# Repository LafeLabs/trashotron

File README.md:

# TRASHOTRON

## [GITHUB.COM/LAFELABS/TRASHOTRON](https://github.com/lafelabs/trashotron)

## [LOCALHOST](http://localhost/)

THIS IS THE UNIFICATION OF GEOMETRON AND TRASH MAGIC IN A SELF-REPLICATING SET

# TRASHOTRON OPTICAL NEURON

 - [boards/trashotron-optical-neuron.brd](boards/trashotron-optical-neuron.brd)
 - [boards/trashotron-optical-neuron.sch](boards/trashotron-optical-neuron.sch) 
 - [buy pcb's at pcbway.com](https://www.pcbway.com/project/shareproject/W224521BSI37_trashotron_optical_neuron_2023_03_06_ae2b0405.html)

### FOR THE LID CUT OUT A 3"X4.5" CARDBOARD RECTANGLE, PAINT AS SHOWN  WITH 1.5 INCH SQURES:

### LAYOUT OF STACK:

### CUT OUT THREE LAYERS OF THESE AND STACK THEM ABOVE THE BOARD 

### BOARD DIMENSIONS:

### LAYER WITH PHOTODIOES PUSHED THROUGH SLITS CUT WITH BOX CUTTER:

### 2 LAYERS OF CARDBOARD WITH 1 INCH SQUARES CUT OUT:

# TRASHOTRON DRIVER

 - [boards/trashotron-driver.brd](boards/trashotron-driver.brd)
 - [boards/trashotron-driver.sch](boards/trashotron-driver.sch) 
 - [link to buy from pcbway.com](www.pcbway.com/project/shareproject/W224521BSI42_trashotron_driver_2023_03_06_1aff405c.html)

Materials

 - [3x$12 = $36 pololu robotics stepper driver](https://www.pololu.com/product/2966)
 - [$15 bojack capacitor kit](https://www.amazon.com/BOJACK-Ceramic-Capacitor-Assortment-Capacitors/dp/B07P7HRGT9/)
 - [$6.32 10k resistors 100 units](https://www.amazon.com/Projects-100EP51210K0-10k-Resistors-Pack/dp/B0185FIOTA/)
 - [$10 50 pin 0.1 inch pitch right angle header strips](https://www.amazon.com/Yohii-Single-Right-Header-Connector/dp/B07C89T16T/)
 - [$7 50 units LM358P op amps](https://www.amazon.com/BOJACK-LM358P-Operational-Amplifier-LM358N/dp/B07WQWPLSP/)
 - [ribbon cable from amazon](https://www.amazon.com/Eowpower-16-5Ft-20Pin-Rainbow-Ribbon/dp/B01NC2L2WB/)

# TRASHOTRON SLIMEZISTOR (ANALOG)
 
The SlimeZistor is a relaxation oscillator which uses an LM358P op amp to charge and discharge a capacitor through some sample which is connected to the two probe wires.  The schematic is as follows, and should be copied and pasted on the bottom of each unit:

These are the kit parts:

Here are links to buy the parts from amazon(enough for about 50 units for about 40 dollars):

 - [$15 bojack capacitor kit](https://www.amazon.com/BOJACK-Ceramic-Capacitor-Assortment-Capacitors/dp/B07P7HRGT9/)
 - [$6.32 10k resistors 100 units](https://www.amazon.com/Projects-100EP51210K0-10k-Resistors-Pack/dp/B0185FIOTA/)
 - [$10 50 pin 0.1 inch pitch right angle header strips](https://www.amazon.com/Yohii-Single-Right-Header-Connector/dp/B07C89T16T/)
 - [$7 50 units LM358P op amps](https://www.amazon.com/BOJACK-LM358P-Operational-Amplifier-LM358N/dp/B07WQWPLSP/)

### [$90 Digikey cart link with part set for 100 units](https://www.digikey.com/short/44n3w1tp)

The circuit board is a 1x2 inch rectangle cut out of thin cardboard like a cereal box:

Remove pins 1,2, and 3 of the 8 pin IC:

Assemble as follows, with 0.1 uF capacitor to the far left, then 1 uF and then the two to the far right which are horizontal are the 10 uF capacitors:

This is a 5x blowup of the board, with parts labeled. Replicate this as a tool for replication to carry with you as you replicate the set:

An array can also be cut out using a laser cutter with the following .svg file(cut out a 4 inch square of this, with the blue layer as raster and black layer as cut):

Here is an .svg of just one board:

This is what the bottom looks like after full assembly:

The enclosure is made from 4 squares each 4x4 inches in size cut from corrugated cardboard using the tools of Geometron:

Stack and glue with Elmer's glue or wheat paste:

Second layer:

Add the circuit board to the box before adding the lid:

Full assembly with lid and rubber bands:

Fully assembled system with speaker connected to audio output and a solar panel connected to the USB power:

## TRASHOTRON SLIMEZISTOR(ANALOG, PCB)

 - [boards/trashotron-slimezistor.brd](boards/trashotron-slimezistor.brd)
 - [boards/trashotron-slimezistor.sch](boards/trashotron-slimezistor.sch) 
 - [buy boards from pcbway.com](https://www.pcbway.com/project/shareproject/SlimeZistor_d6c918ee.html)
 - [wikipedia link about relaxation oscillator](https://en.wikipedia.org/wiki/Relaxation_oscillator)

The board is 2x1 inch and it fits in a cavity centered in a 3 inch by 3 inch cardboard square with ports as shown.  Find USB and audio in the trash and another cable from the trash with two wires .  This can run on a direct solar panel, since it should work at random voltages.    

## RESISTOR AND CAPACITOR ORDER

 - [30M resistor](https://www.digikey.com/en/products/detail/yageo/HHV-25FR-52-30M/2813033)
 - [10 k resistor](https://www.digikey.com/en/products/detail/stackpole-electronics-inc/CF18JT10K0/1741566)
 - [0.1 uF capacitor](https://www.digikey.com/en/products/detail/kyocera-avx/SR211C104KARTR1/3066560)
 - [0.47 uF capacitor](https://www.digikey.com/en/products/detail/kyocera-avx/SR215E474MAR/1836459)
 - [10 uF capacitor](https://www.digikey.com/en/products/detail/kemet/C322C106K3R5TA/6562379)
 - [link to whole digikey cart](https://www.digikey.com/short/44n3w1tp)
 
## TRASHOTRON HOMESCREEN

## TRASHOTRON HYPERCUBE

self-replicating cubes from cardboard trash based on a 4 inch by 4 inch square.

 - [boards/trashotron-hypercube-v1.brd](boards/trashotron-hypercube.brd)
 - [boards/trashotron-hypercube-v1.sch](boards/trashotron-hypercube.sch)

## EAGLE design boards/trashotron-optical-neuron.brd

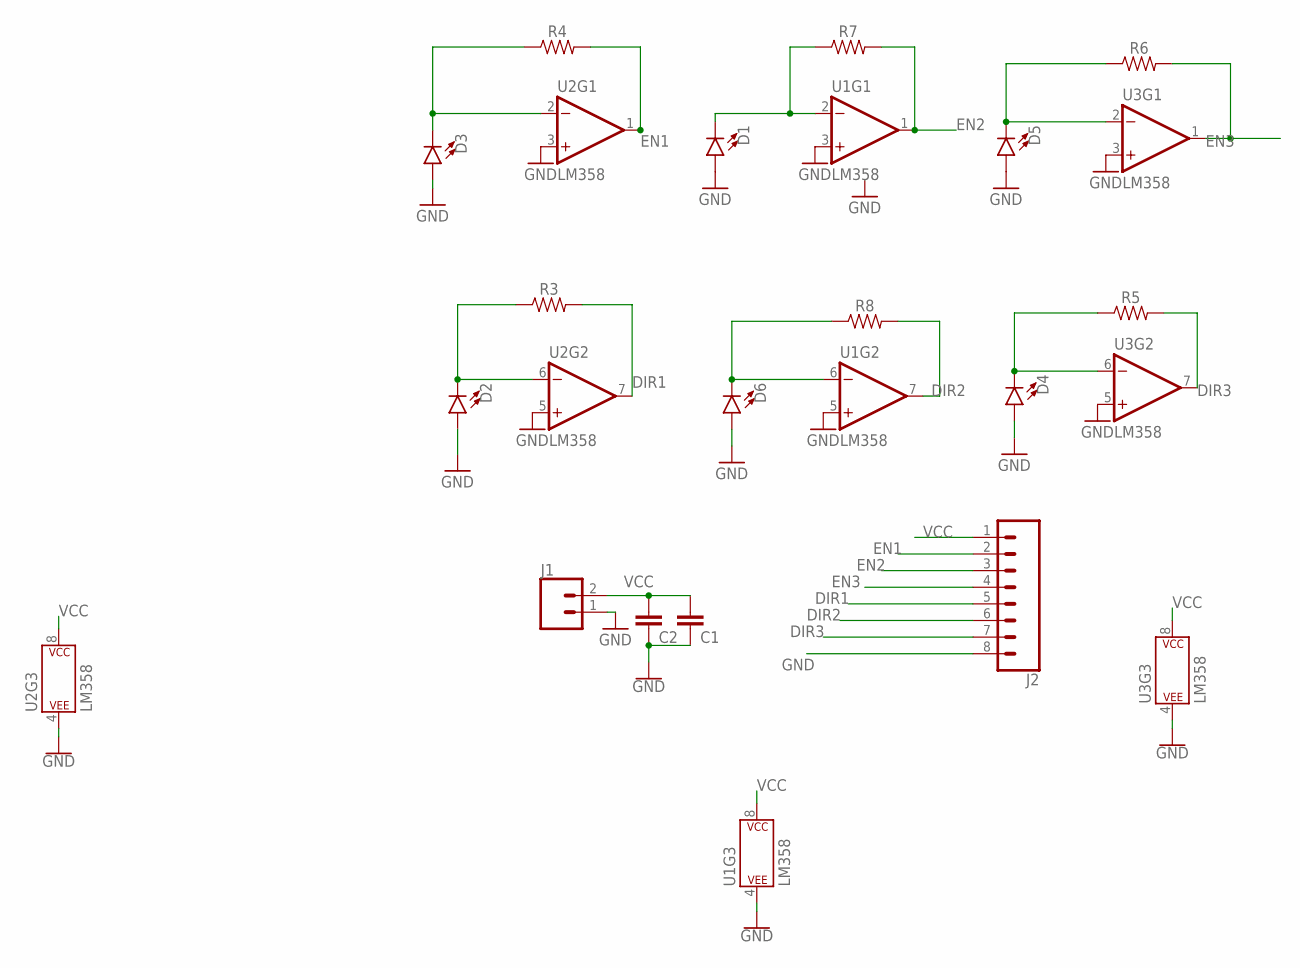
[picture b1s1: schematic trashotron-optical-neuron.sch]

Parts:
C1, C2: C-EU050-050X075; C050-050X075
D1, D2, D3, D4, D5, D6: LED3MM; LED_3MM
J1: CONN_02; 1X02
J2: CONN_08"; 1X08
R3, R4, R5, R6, R7, R8: AXIAL-0.3
U1, U2, U3: LM358; DIP08

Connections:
DIR1: J2.5, R3.P$2 (2), U2.7 (OUT)
DIR2: J2.6, R8.P$2 (2), U1.7 (OUT)
DIR3: J2.7, R5.P$2 (2), U3.7 (OUT)
EN1: J2.2, R4.P$2 (2), U2.1 (OUT)
EN2: J2.3, R7.P$2 (2), U1.1 (OUT)
EN3: J2.4, R6.P$2 (2), U3.1 (OUT)
GND: C1.1, C2.1, D1.A, D2.A, D3.A, D4.A, D5.A, D6.A, J1.1, J2.8, U1.3 (+IN), U1.4 (P$V-), U1.5 (+IN), U2.3 (+IN), U2.4 (P$V-), U2.5 (+IN), U3.3 (+IN), U3.4 (P$V-), U3.5 (+IN)
unnamed: D1.K (C), R7.P$1 (1), U1.2 (-IN)
unnamed: D3.K (C), R4.P$1 (1), U2.2 (-IN)
unnamed: D2.K (C), R3.P$1 (1), U2.6 (-IN)
unnamed: D4.K (C), R5.P$1 (1), U3.6 (-IN)
unnamed: D5.K (C), R6.P$1 (1), U3.2 (-IN)
unnamed: D6.K (C), R8.P$1 (1), U1.6 (-IN)
VCC: C1.2, C2.2, J1.2, J2.1, U1.8 (P$V+), U2.8 (P$V+), U3.8 (P$V+)

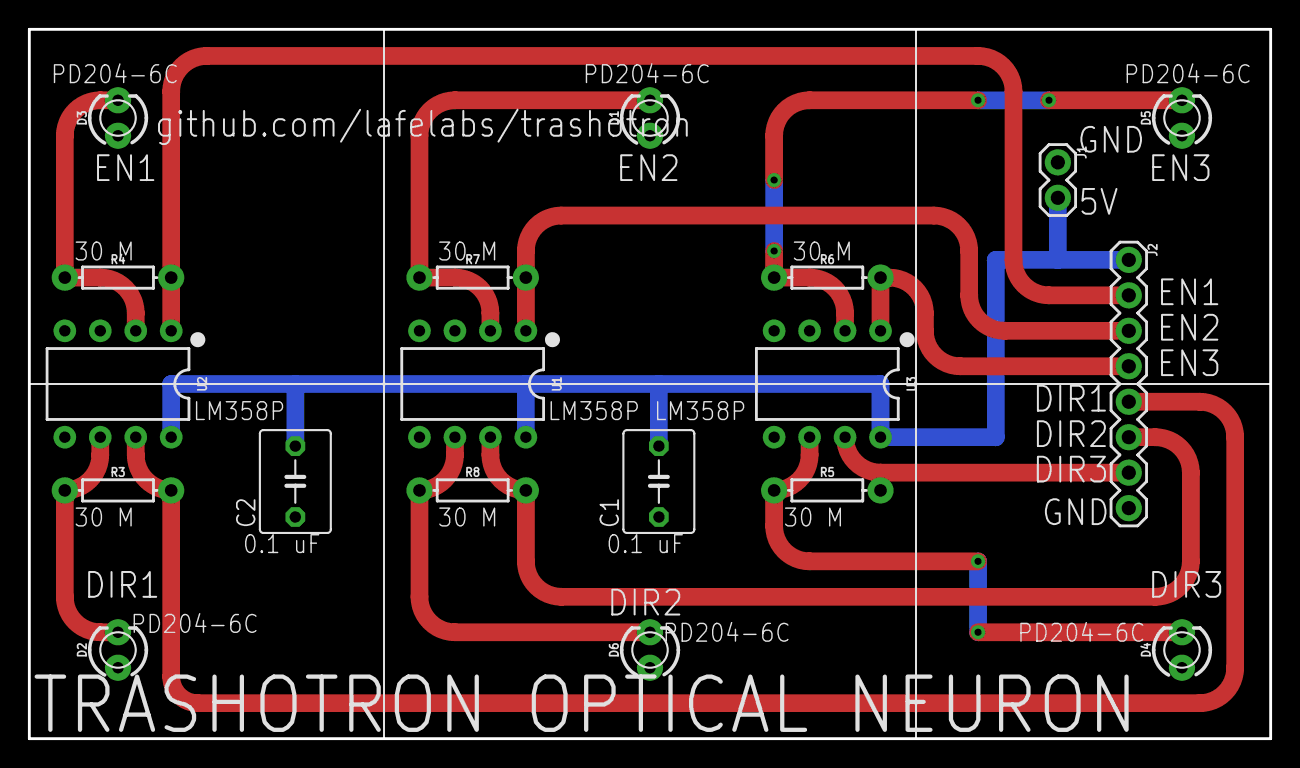
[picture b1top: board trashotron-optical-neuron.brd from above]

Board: 2 copper layers, 88.9 x 50.8 mm, 19 parts (0 on the bottom side), 14 nets.

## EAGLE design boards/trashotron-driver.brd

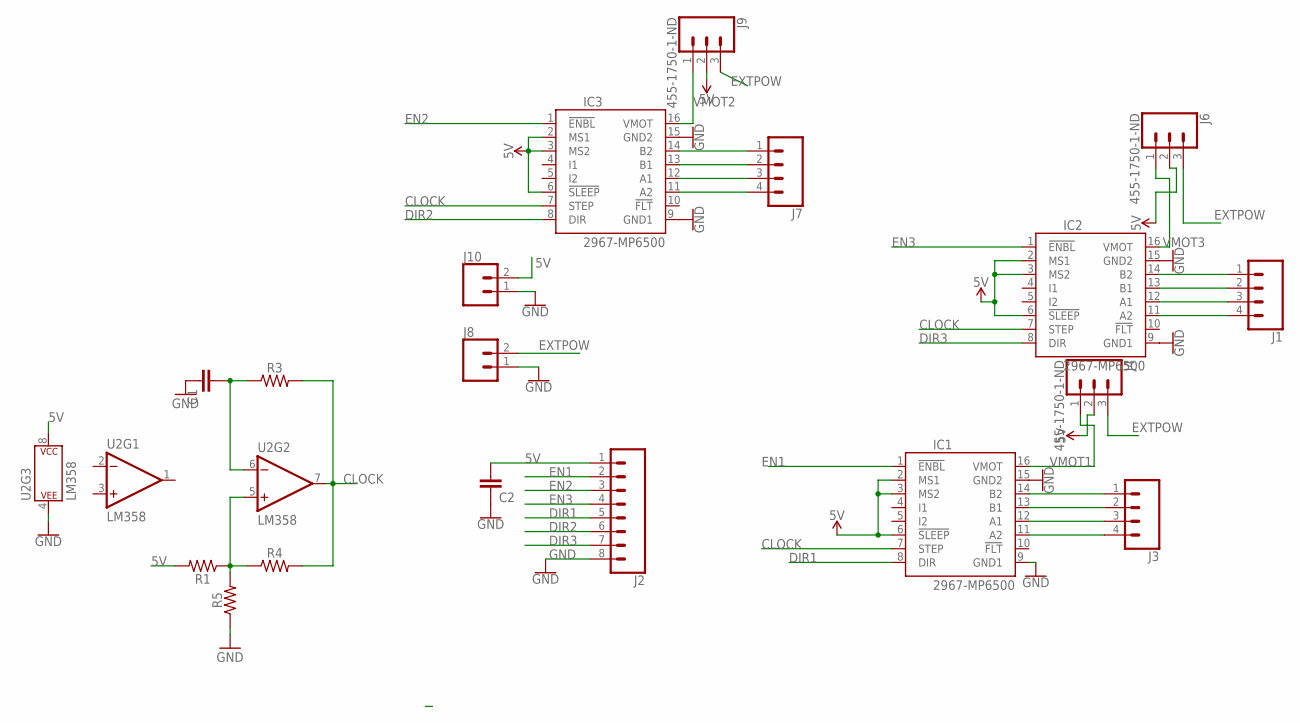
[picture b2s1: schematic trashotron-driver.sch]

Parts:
C1, C2: C-EU050-050X075; C050-050X075
IC1, IC2, IC3: 2967-MP6500; MP6500
J1, J3, J7: CONN_04; 1X04
J2: CONN_08"; 1X08
J4, J6, J9: 455-1750-1-ND; 1X03
J8, J10: CONN_02; 1X02
R1, R3, R4, R5: AXIAL-0.3
U2: LM358; DIP08

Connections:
5V: C2.2, IC1.2 (MS1), IC1.3 (MS2), IC1.6 (!SLEEP), IC2.2 (MS1), IC2.3 (MS2), IC2.6 (!SLEEP), IC3.2 (MS1), IC3.3 (MS2), IC3.6 (!SLEEP), J2.1, J4.2, J6.2, J9.2, J10.2, R1.P$2 (2), U2.8 (P$V+)
CLOCK: IC1.7 (STEP), IC2.7 (STEP), IC3.7 (STEP), R3.P$2 (2), R4.P$2 (2), U2.7 (OUT)
DIR1: IC1.8 (DIR), J2.5
DIR2: IC3.8 (DIR), J2.6
DIR3: IC2.8 (DIR), J2.7
EN1: IC1.1 (!ENBL), J2.2
EN2: IC3.1 (!ENBL), J2.3
EN3: IC2.1 (!ENBL), J2.4
EXTPOW: J4.3, J6.3, J8.2, J9.3
GND: C1.1, C2.1, IC1.9 (GND1), IC1.15 (GND2), IC2.9 (GND1), IC2.15 (GND2), IC3.9 (GND1), IC3.15 (GND2), J2.8, J8.1, J10.1, R5.P$1 (1), U2.4 (P$V-)
unnamed: IC3.14 (B2), J7.1
unnamed: IC3.13 (B1), J7.2
unnamed: IC1.14 (B2), J3.1
unnamed: IC1.13 (B1), J3.2
unnamed: IC1.12 (A1), J3.3
unnamed: IC1.11 (A2), J3.4
unnamed: IC2.14 (B2), J1.1
unnamed: IC2.13 (B1), J1.2
unnamed: IC2.12 (A1), J1.3
unnamed: IC2.11 (A2), J1.4
unnamed: IC3.12 (A1), J7.3
unnamed: IC3.11 (A2), J7.4
unnamed: C1.2, R3.P$1 (1), U2.6 (-IN)
unnamed: R1.P$1 (1), R4.P$1 (1), R5.P$2 (2), U2.5 (+IN)
VMOT1: IC1.16 (VMOT), J4.1
VMOT2: IC3.16 (VMOT), J9.1
VMOT3: IC2.16 (VMOT), J6.1

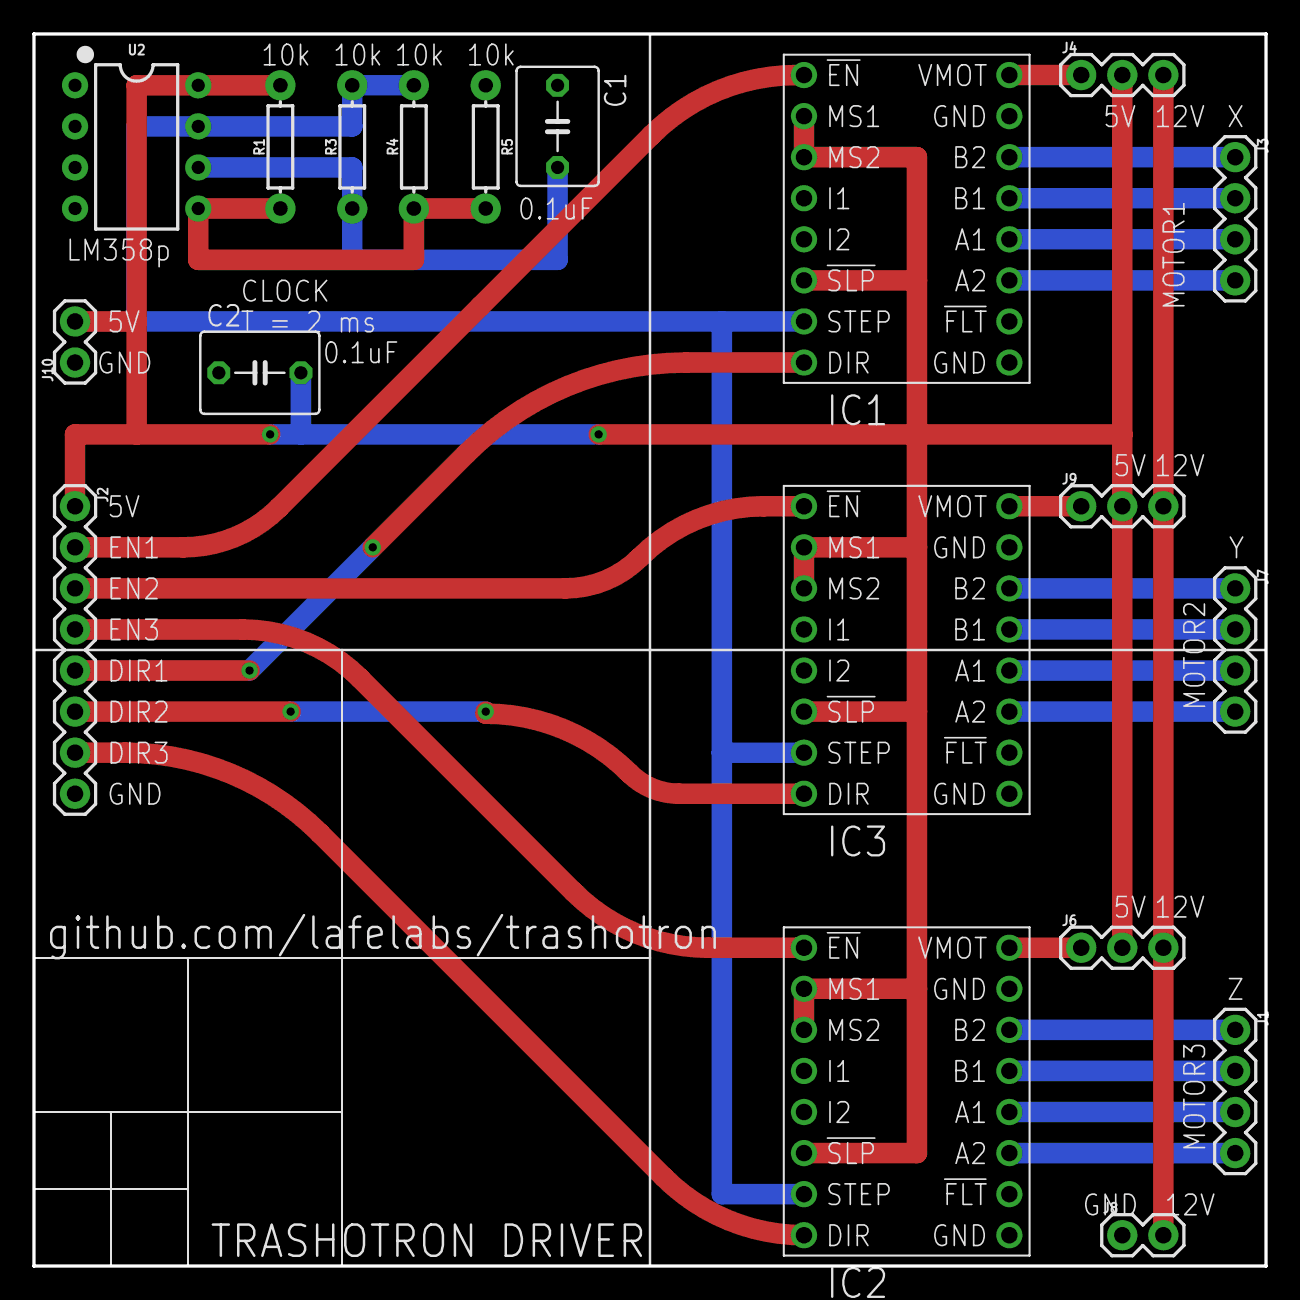
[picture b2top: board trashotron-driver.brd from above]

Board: 2 copper layers, 76.2 x 76.2 mm, 19 parts (0 on the bottom side), 27 nets.

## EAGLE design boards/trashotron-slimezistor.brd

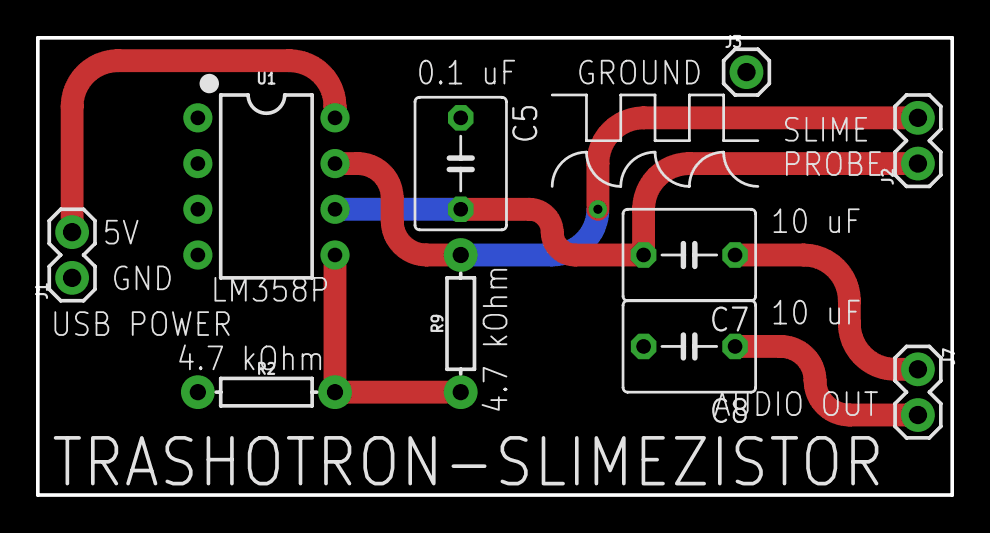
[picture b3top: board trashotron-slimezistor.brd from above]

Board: 2 copper layers, 50.8 x 25.4 mm, 10 parts (0 on the bottom side), 7 nets.

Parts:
C5, C7, C8: C050-050X075
J1, J2, J7: 1X02
J3: 1X01
R2, R9: AXIAL-0.3
U1: LM358; DIP08

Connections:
GND: C5.1, C8.2, J1.1, J3.1, R2.P$1, U1.4
unnamed: J2.2, R9.P$2, U1.7
unnamed: R2.P$2, R9.P$1, U1.5
unnamed: C5.2, C7.2, J2.1, U1.6
unnamed: C8.1, J7.2
unnamed: C7.1, J7.1
VCC: J1.2, U1.8

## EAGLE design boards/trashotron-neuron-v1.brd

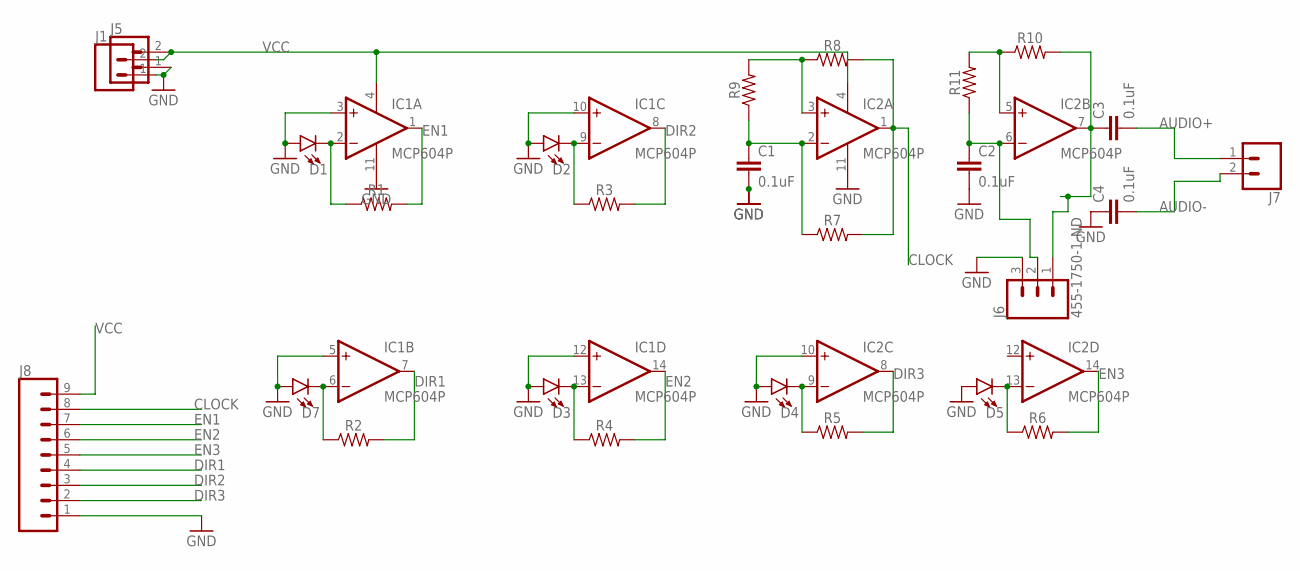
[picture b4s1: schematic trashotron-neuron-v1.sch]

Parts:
C1, C2, C3, C4: 0.1uF; CAP-PTH-SMALL-KIT
D1, D2, D3, D4, D5, D7: LED3MM; LED_3MM
IC1, IC2: MCP604P; DIL14
J1, J5, J7: CONN_02; 1X02
J6: 455-1750-1-ND; 1X03
J8: CONN_09; 1X09
R1, R2, R3, R4, R5, R6, R7, R8, R9, R10, R11: AXIAL-0.3

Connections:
AUDIO+: C3.2, J7.1
AUDIO-: C4.2, J7.2
CLOCK: IC2.1 (OUT), J8.8, R7.P$2 (2), R8.P$2 (2)
DIR1: IC1.7 (OUT), J8.4, R2.P$2 (2)
DIR2: IC1.8 (OUT), J8.3, R3.P$2 (2)
DIR3: IC2.8 (OUT), J8.2, R5.P$2 (2)
EN1: IC1.1 (OUT), J8.7, R1.P$2 (2)
EN2: IC1.14 (OUT), J8.6, R4.P$2 (2)
EN3: IC2.14 (OUT), J8.5, R6.P$2 (2)
GND: C1.2, C2.2, C4.1, D1.A, D2.A, D3.A, D4.A, D5.A, D7.A, IC1.3 (+IN), IC1.5 (+IN), IC1.10 (+IN), IC1.11 (V-), IC1.12 (+IN), IC2.10 (+IN), IC2.11 (V-), J1.1, J5.1, J6.3, J8.1
unnamed: D1.K (C), IC1.2 (-IN), R1.P$1 (1)
unnamed: D7.K (C), IC1.6 (-IN), R2.P$1 (1)
unnamed: D2.K (C), IC1.9 (-IN), R3.P$1 (1)
unnamed: D4.K (C), IC2.9 (-IN), R5.P$1 (1)
unnamed: D5.K (C), IC2.13 (-IN), R6.P$1 (1)
unnamed: D3.K (C), IC1.13 (-IN), R4.P$1 (1)
unnamed: C2.1, IC2.6 (-IN), J6.2, R11.P$1 (1)
unnamed: IC2.3 (+IN), R8.P$1 (1), R9.P$2 (2)
unnamed: IC2.5 (+IN), R10.P$1 (1), R11.P$2 (2)
unnamed: C1.1, IC2.2 (-IN), R7.P$1 (1), R9.P$1 (1)
unnamed: C3.1, IC2.7 (OUT), J6.1, R10.P$2 (2)
VCC: IC1.4 (V+), IC2.4 (V+), J1.2, J5.2, J8.9

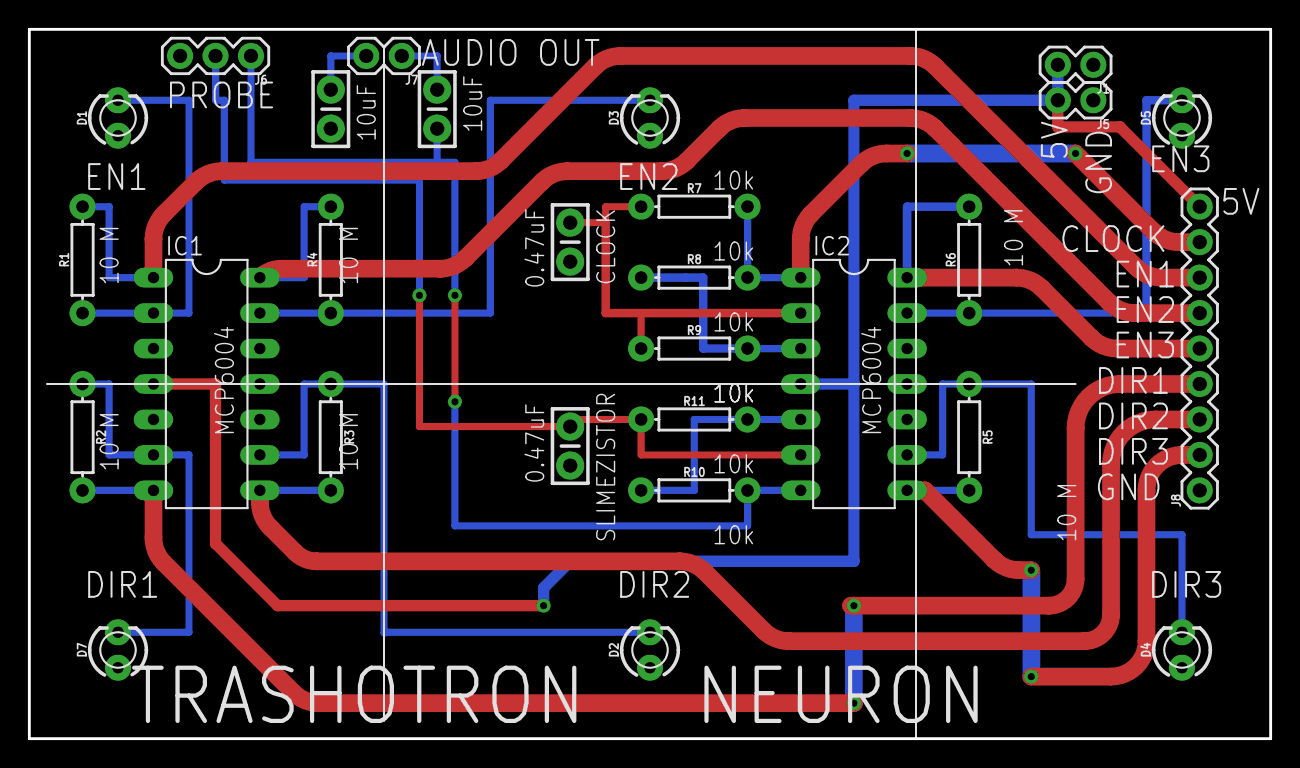
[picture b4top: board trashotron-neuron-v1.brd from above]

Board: 2 copper layers, 88.9 x 50.8 mm, 28 parts (0 on the bottom side), 22 nets.

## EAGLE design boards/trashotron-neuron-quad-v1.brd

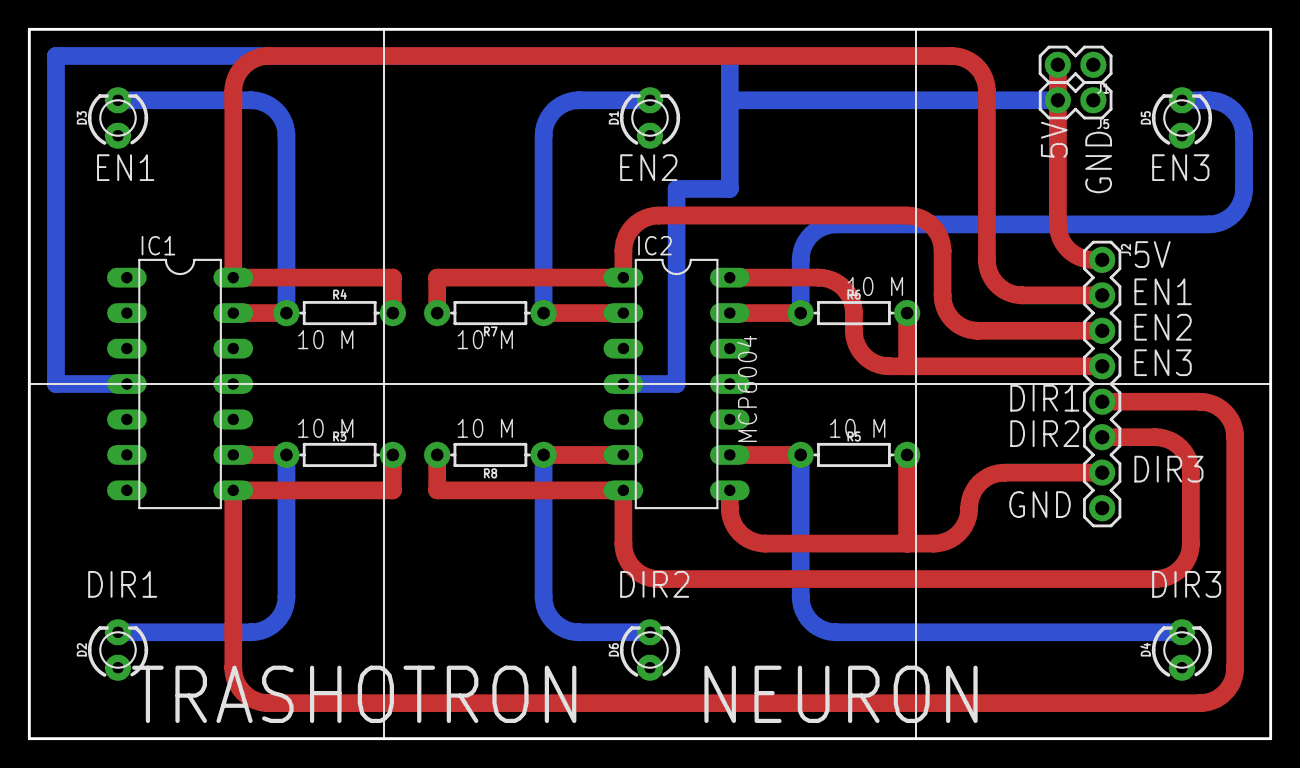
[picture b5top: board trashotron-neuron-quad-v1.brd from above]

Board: 2 copper layers, 88.9 x 50.8 mm, 17 parts (0 on the bottom side), 14 nets.

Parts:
D1, D2, D3, D4, D5, D6: LED_3MM
IC1, IC2: MCP604P; DIL14
J1, J5: 1X02
J2: 1X08
R3, R4, R5, R6, R7, R8: AXIAL-0.3

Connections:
DIR1: IC1.8, J2.5, R3.P$2
DIR2: IC2.7, J2.6, R8.P$2
DIR3: IC2.8, J2.7, R5.P$2
EN1: IC1.14, J2.2, R4.P$2
EN2: IC2.1, J2.3, R7.P$2
EN3: IC2.14, J2.4, R6.P$2
GND: D1.A, D2.A, D3.A, D4.A, D5.A, D6.A, IC1.10, IC1.11, IC1.12, IC2.3, IC2.5, IC2.10, IC2.11, IC2.12, J1.1, J2.8, J5.1
unnamed: D1.K, IC2.2, R7.P$1
unnamed: D2.K, IC1.9, R3.P$1
unnamed: D6.K, IC2.6, R8.P$1
unnamed: D4.K, IC2.9, R5.P$1
unnamed: D5.K, IC2.13, R6.P$1
unnamed: D3.K, IC1.13, R4.P$1
VCC: IC1.4, IC2.4, J1.2, J2.1, J5.2

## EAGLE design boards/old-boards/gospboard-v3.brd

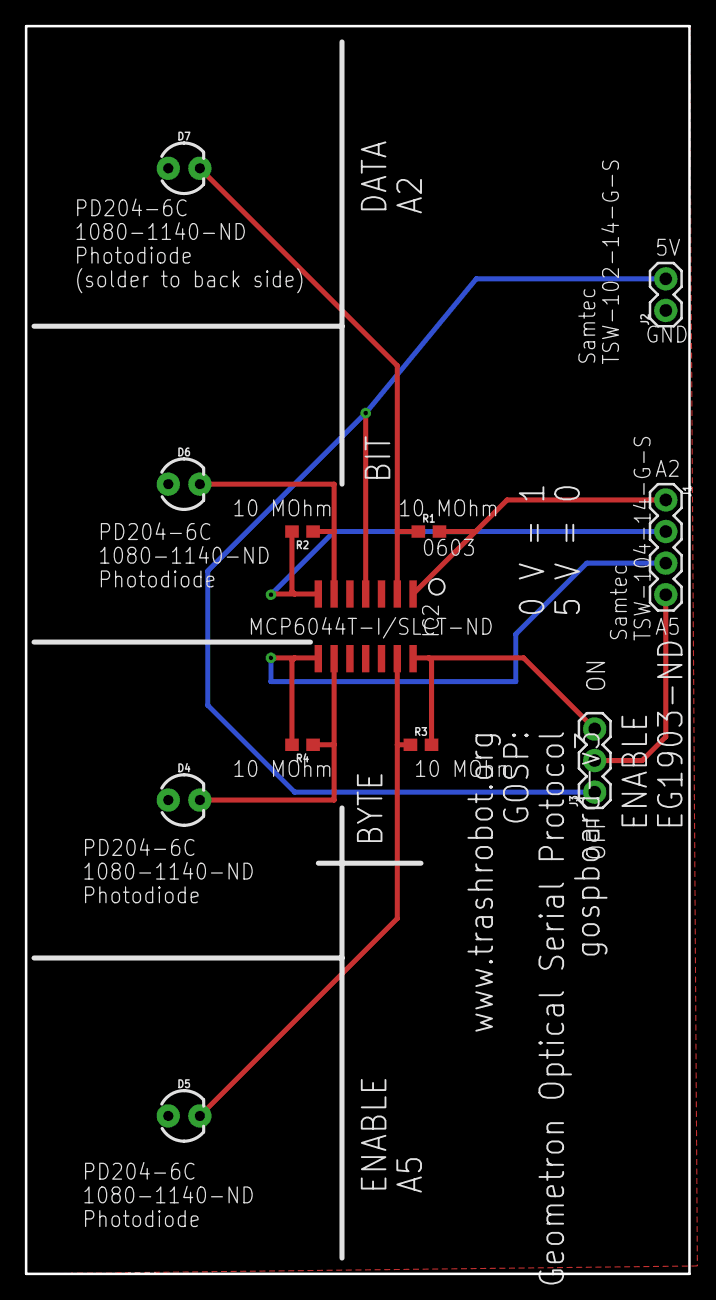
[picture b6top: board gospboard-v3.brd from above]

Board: 2 copper layers, 53.3 x 100.3 mm, 12 parts (0 on the bottom side), 11 nets.

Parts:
D4, D5, D6, D7: LED_3MM
IC2: MCP604SL; SO14
J1: 1X04
J2: 1X02
J3: 455-1750-1-ND; 1X03
R1, R2, R3, R4: 10M; 0603

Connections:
ENABLE: IC2.14, J3.3, R3.2
GND: D4.A, D5.A, D6.A, D7.A, IC2.3, IC2.5, IC2.10, IC2.11, IC2.12, J2.1
unnamed: J1.4, J3.2
unnamed: D7.K, IC2.2, R1.1
unnamed: IC2.8, J1.3, R4.2
unnamed: D6.K, IC2.6, R2.1
unnamed: D4.K, IC2.9, R4.1
unnamed: IC2.7, J1.2, R2.2
unnamed: D5.K, IC2.13, R3.1
unnamed: IC2.4, J2.2, J3.1
PIN1: IC2.1, J1.1, R1.2

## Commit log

2023-03-01 trash printer copied over from phreakotron
2023-03-01 trashonomicon
2023-03-01 TRASHOTRON DOES THE THING!
2023-03-02 boards!
2023-03-02 trashotron board geometry roughed out with correct dimensions
2023-03-02 trashotron board mostly laid out in schematic
2023-03-03 trashotron driver board and trashotron neuron board are both done in a first draft
2023-03-03 board development and a longer default glyph
2023-03-04 lots of work on pcb layout
2023-03-04 massive trashotron development
2023-03-04 documentation for replication
2023-03-04 update the ruler geometron svg file
2023-03-04 changed all the names to make them simpler
2023-03-05 trashotron-hypercube is a thing
2023-03-05 remove redundant hypercube
2023-03-05 trashotron homescreen image in readme
2023-03-05 update trashotron and readme
2023-03-05 added some layout images and fixed bugs in the hypercube
2023-03-05 slimezistor lid is a 3 inch square
2023-03-06 this version of the boards is now all tested out on solderless breadboard
2023-03-07 boards done and ordered, added a loop trashotron page
2023-03-09 ordering resistors and capacitors
2023-03-09 slimezistor 4 inch square cutout with dimensions
2023-03-10 image of slimezistor in the sand added
2023-03-11 audio analysis in jupyter and update of schematic for slimezistor
2023-03-13 lots of photos of slimezistor, enough for replicator scroll hopefully
2023-03-13 more photos
2023-03-15 building all the html robots
2023-03-16 icon printer, lots of random robot work
2023-03-16 lots of photos added
2023-03-19 integrated trashbook into this to document and replicate it as a single set
2023-03-19 slimezistor scroll
2023-03-19 css robot and p5js robot
2023-03-20 various robotics additions
2023-03-20 expanding the trashonomicon scroll set
2023-03-20 adding in the full geometron and more scrolls
2023-03-20 replicator replicating
2023-03-20 fixing replicator
2023-03-21 system development
2023-03-21 driver and neuron and clock
2023-03-21 optical neuron image update
2023-03-21 css robot scroll
2023-03-22 neuron docs
2023-03-22 much scroll creation and work
2023-03-22 wall printer now is set up to work with solenoid and dual hoists for spray paint etch-a-sketch functionality
2023-03-22 slimeotron!
2023-03-23 tiles is a thing. split it off from here though. trashotron has a new function to set trashotron.
2023-03-24 fixed a couple broken links to pcb's
2023-03-24 tiles/board.html...this needs to be its own repository
2023-03-24 slimeotron uses the same function as trashotron now, and so has portrait mode and resize
2023-03-24 Update neuron
2023-03-24 optical neuron qr code
2023-03-24 qrcode update
2023-03-24 driver qrcode
2023-03-24 Update driver
2023-03-27 wallprinter.html is the real deal! it has programming functionality which needs to replicate to the main trashotron robot
2023-03-27 Update home
2023-03-27 xyzprobe has glyph editor now! same keyboard as the wall printer
2023-03-27 wall printer and xyz work
2023-03-27 loopotron!
2023-03-31 fixed bug in the frequency calculation
2023-03-31 slimezistor has its own page
2023-04-01 fixed the geometry of the spectrum display weird loop bug
2023-04-01 wallprinter updated to have ability to design a glyph on the wall with canvas
2023-04-02 slimezistor documentation work
2023-04-02 added useful images
2023-04-02 mobile wall printer
2023-04-03 BOM for slimezistor, update README to have payment links
2023-04-03 wallprinter is a fork of trashotron just for the scroll to be self-replicating
2023-04-04 welcome to the dirtnet!
2023-04-04 neuron scroll
2023-04-06 added diagonal lines to geometron language in wallprinter.html
2023-04-06 wallboard.html
2023-04-07 wall writer is really coming together
2023-04-07 slime improvements
2023-04-09 dtmf really working now
2023-04-09 scroll improvements
2023-04-10 tile board with squares
2023-04-11 trashpod
2023-04-11 added more images
2023-04-11 trashmagic!
2023-04-11 trashpod is massively streamlined
2023-04-11 slimebeats
2023-04-12 SLIMEZISTOR TILES ARE FILLING UP MIDDLE EARTH WITH SYNTHESIZERS
2023-04-13 dtmf trashotron is basically working
2023-04-14 trashotron might be ready to start taking data! it's close
2023-04-14 finally taking what looks to be good JSON data
2023-04-14 fixed absurd bug where I re-used the variable name "z"
2023-04-15 lots of data!
2023-04-17 finally got the dtmf keypad to work with nice looking keys
2023-04-17 projector.html now works in trashotron/slimezistor/tiles
2023-04-17 synth images
2023-04-20 zine
2023-04-20 this is mostly put together now!
2023-04-20 cube
2023-04-20 qrcodes
2023-04-22 so much data, lots and lots of data
2023-04-22 browser o slime
2023-04-22 lots of good new data of a trajectory to test out analysis code on
2023-04-23 files.txt lists the files in a folder when you click on the folder in the slime data browser
2023-04-23 sloanslakedotart
2023-04-30 some little python updates

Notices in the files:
parts and their libraries:
SparkFun-LED: Licensing: Creative Commons ShareAlike 4.0 International - https://creativecommons.org/licenses/by-sa/4.0
